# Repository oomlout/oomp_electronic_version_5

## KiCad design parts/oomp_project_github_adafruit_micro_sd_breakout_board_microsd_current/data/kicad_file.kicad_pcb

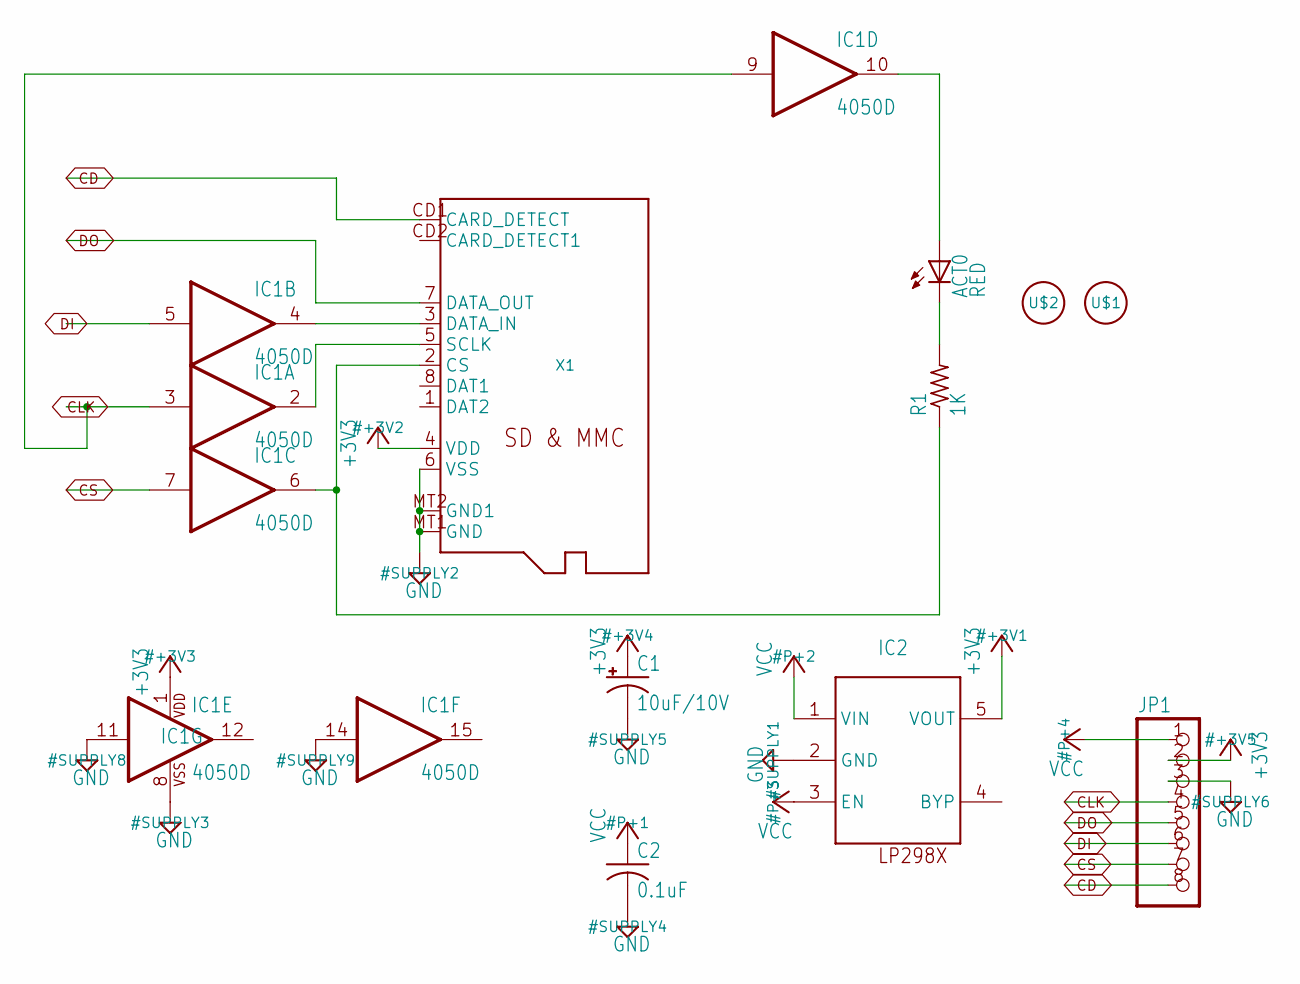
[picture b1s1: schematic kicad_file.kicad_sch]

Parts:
ACT0: RED; CHIP-LED0805
C1: 10uF/10V; A_3216-18R
C2: 0.1uF; C0805K
IC1: 4050D; SO16
IC2: LP298XS; SOT23-5L
JP1: PINHD-1X8BIG; 1X08-BIG
R1: 1K; R0805
U$1, U$2: FIDUCIAL; FIDUCIAL_1MM
X1: MICROSD

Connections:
+3V3: C1.+, IC1.1 (VDD), IC2.5 (VOUT), JP1.2, X1.4 (VDD)
CD: JP1.8, X1.CD1 (CARD_DETECT)
CLK: IC1.3 (I), IC1.9 (I), JP1.4
CS: IC1.7 (I), JP1.7
DI: IC1.5 (I), JP1.6
DO: JP1.5, X1.7 (DATA_OUT)
GND: C1.-, C2.2, IC1.8 (VSS), IC1.11 (I), IC1.14 (I), IC2.2 (GND), JP1.3, X1.6 (VSS), X1.MT1 (GND), X1.MT2 (GND1)
unnamed: ACT0.A, IC1.10 (O)
unnamed: IC1.2 (O), X1.5 (SCLK)
unnamed: IC1.6 (O), R1.1, X1.2 (CS)
unnamed: ACT0.C, R1.2
unnamed: IC1.4 (O), X1.3 (DATA_IN)
VCC: C2.1, IC2.1 (VIN), IC2.3 (EN), JP1.1

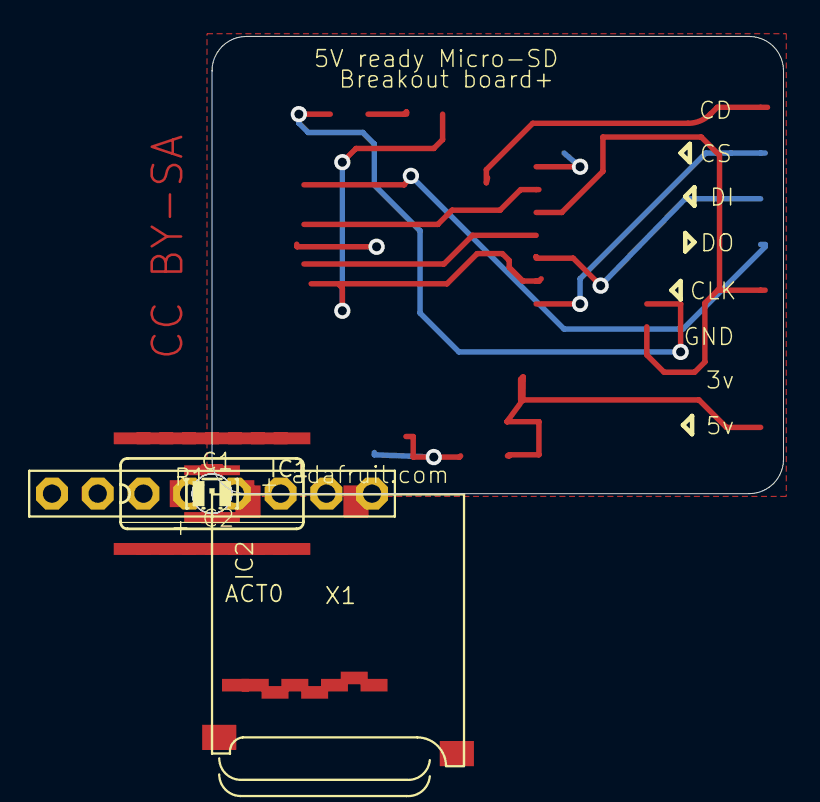
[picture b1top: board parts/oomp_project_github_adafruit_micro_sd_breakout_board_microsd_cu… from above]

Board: 16 copper layers, 31.8 x 25.4 mm, 14 parts (0 on the bottom side), 13 nets.

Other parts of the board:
UNK_HOLE_0: dummyfp0
UNK_HOLE_1: dummyfp1
UNK_HOLE_2: dummyfp2
UNK_HOLE_3: dummyfp3

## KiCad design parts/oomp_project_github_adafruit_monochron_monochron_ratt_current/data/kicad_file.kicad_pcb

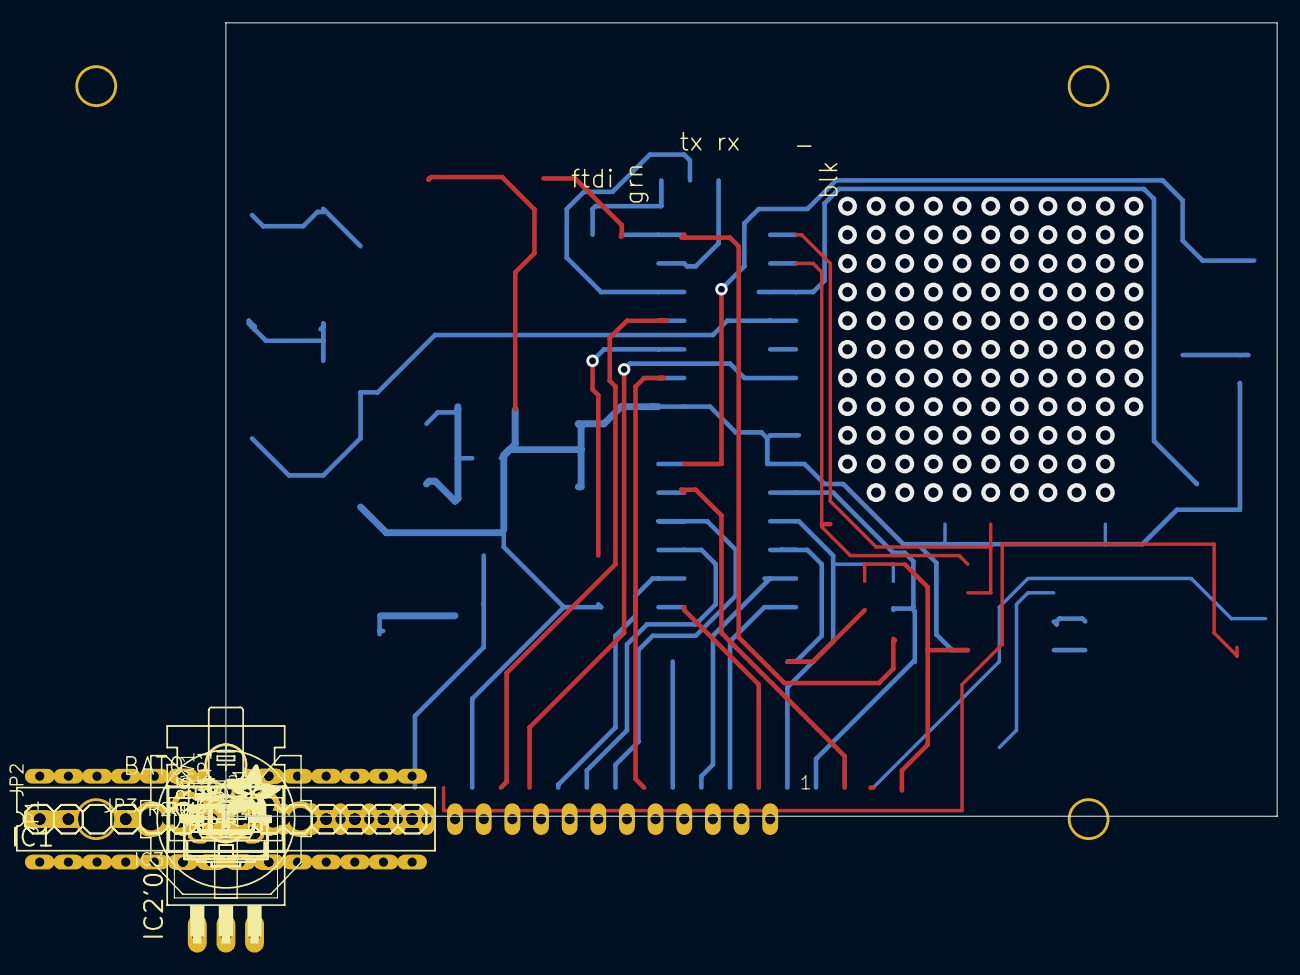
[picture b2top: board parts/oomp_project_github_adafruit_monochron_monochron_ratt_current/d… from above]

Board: 16 copper layers, 93.2 x 70.4 mm, 33 parts (1 on the bottom side), 17 nets.

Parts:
BAT0: CR1220; CR1220-THM
C1, C5: 0.1uF; C025-025X050
D1: 1N4004; DO41-10
IC1: ATMEGA168-20P; DIL28-3
IC2: 78L05Z; TO92
IC2'0: 7805T; TO220H
IC3: DS1307; DIL08
ISP0: ISP; 2X03
JP1: BRK1; 1X14
JP2: BRK2; 1X14
JP3: FTDI; 1X06
LED1: Red; LED3MM
Q1: 32.768; TC38H
R1: 1k; 0207_10
R2, R2'0: 100; 0207_10
R3, R4, R5, R6, R7: 1K; 0207_10
R8, R9: 2.2k; 0207_10
R10: 10K; 0207_10
S1, S2, S3: B3F-31XX
SP1: SPEAKER/PS12; PS12
SW1: OS102011MA1Q
TM1: 10K; CA6H
U$1: TS12864A; TS12864
U$2: http___www.ladyada.net_make_monochron

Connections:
+9V: C1.2, S1.1, S2.2, TM1.A
A: JP1.2, SW1.MT2
ALARM_SW: R6.1, R9.2
DB1: JP1.13, R3.1
DB2: JP1.12, R3.2
DB3: JP1.11, JP2.2
MOSI: IC1.4, JP2.1
unnamed: LED1.K, Q1.1, R7.1
unnamed: JP3.1, R2.2
unnamed: JP3.2, R2.1
unnamed: D1.C, S2.1
unnamed: R8.2, R9.1
unnamed: BAT0.+1, LED1.A, U$1.20
RST: IC1.5, R1.1, R5.1
RXD: R1.2, R5.2
SWITCHES: IC2'0.1, IC3.1, R7.2
VCC: IC1.2, IC2.1, IC3.2, ISP0.1, JP1.4, JP3.4, R2'0.2, R8.1, SP1.P$2, SW1.2, TM1.E

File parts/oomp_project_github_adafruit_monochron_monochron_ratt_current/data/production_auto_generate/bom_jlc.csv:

Comment,Designator,Footprint,LCSC Part #
,"S1,S2,S3",ratt-import-fps:B3F-31XX,
,U$2,ratt-import-fps:http___www.ladyada.net_make_monochron,
0.1uF,"C1,C5",ratt-import-fps:C025-025X050,
100,"R2,R2'0",ratt-import-fps:0207_10,
10K,R10,ratt-import-fps:0207_10,
10K,TM1,ratt-import-fps:CA6H,
1k,R1,ratt-import-fps:0207_10,
1K,"R3,R4,R5,R6,R7",ratt-import-fps:0207_10,
1N4004,D1,ratt-import-fps:DO41-10,
2.2k,"R8,R9",ratt-import-fps:0207_10,
32.768,Q1,ratt-import-fps:TC38H,
7805T,IC2'0,ratt-import-fps:TO220H,
78L05Z,IC2,ratt-import-fps:TO92,
ATMEGA168-20P,IC1,ratt-import-fps:DIL28-3,
BRK1,JP1,ratt-import-fps:1X14,
BRK2,JP2,ratt-import-fps:1X14,
CR1220,BAT0,ratt-import-fps:CR1220-THM,
DS1307,IC3,ratt-import-fps:DIL08,
FTDI,JP3,ratt-import-fps:1X06,
ISP,ISP0,ratt-import-fps:2X03,
OS102011MA1Q,SW1,ratt-import-fps:OS102011MA1Q,
Red,LED1,ratt-import-fps:LED3MM,
TS12864A,U$1,ratt-import-fps:TS12864,

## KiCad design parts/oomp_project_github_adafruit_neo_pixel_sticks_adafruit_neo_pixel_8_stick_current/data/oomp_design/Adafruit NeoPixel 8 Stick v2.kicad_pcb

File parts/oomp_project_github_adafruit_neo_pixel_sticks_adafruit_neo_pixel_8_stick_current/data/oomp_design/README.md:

# OOMP KiCad design copy

Open `Adafruit NeoPixel 8 Stick v2.kicad_pro` (or the `.kicad_pcb` / `.kicad_sch`) in KiCad. Local OOMP libraries are under `libraries/`. Original inputs are preserved in [../original/](../original/).

Only verified unchanged installed KiCad defaults were renamed. Modified, custom, unmatched and unavailable items remain unchanged. Soldering variants are never swapped during conversion. Existing pad coordinates, nets and UUIDs are preserved.

See [conversion_report.yaml](conversion_report.yaml) for every conversion and skip. Copy this directory before editing; regeneration refuses to overwrite edited design files.

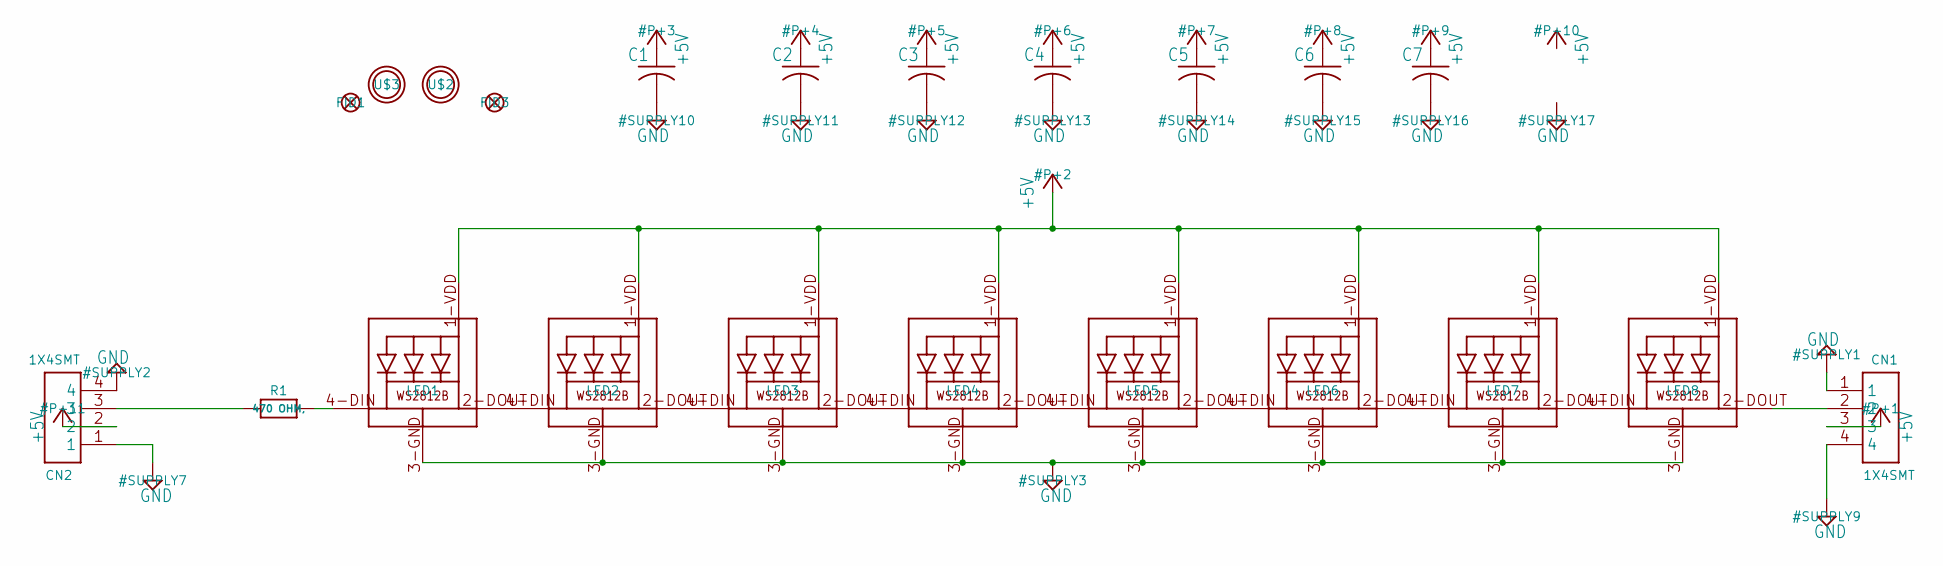
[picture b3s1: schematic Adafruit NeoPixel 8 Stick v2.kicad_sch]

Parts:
C1, C2, C3, C4, C5, C6, C7: C-USC0805K; C0805K
CN1, CN2: 1X4SMT; 1X4-SMT
FID1, FID3: FIDUCIAL""; FIDUCIAL_1MM
LED1, LED2, LED3, LED4, LED5, LED6, LED7, LED8: WS2812B5050; WS2812B
R1: 470 OHM,; _0805MP
U$2, U$3: MOUNTINGHOLE2.0; MOUNTINGHOLE_2.0_PLATED

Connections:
+5V: C1.1, C2.1, C3.1, C4.1, C5.1, C6.1, C7.1, CN1.3, CN2.2, LED1.1-VDD (VDD), LED2.1-VDD (VDD), LED3.1-VDD (VDD), LED4.1-VDD (VDD), LED5.1-VDD (VDD), LED6.1-VDD (VDD), LED7.1-VDD (VDD), LED8.1-VDD (VDD)
GND: C1.2, C2.2, C3.2, C4.2, C5.2, C6.2, C7.2, CN1.1, CN1.4, CN2.1, CN2.4, LED1.3-GND (GND), LED2.3-GND (GND), LED3.3-GND (GND), LED4.3-GND (GND), LED5.3-GND (GND), LED6.3-GND (GND), LED7.3-GND (GND), LED8.3-GND (GND)
unnamed: LED1.2-DOUT (DO), LED2.4-DIN (DI)
unnamed: LED2.2-DOUT (DO), LED3.4-DIN (DI)
unnamed: LED3.2-DOUT (DO), LED4.4-DIN (DI)
unnamed: LED4.2-DOUT (DO), LED5.4-DIN (DI)
unnamed: LED5.2-DOUT (DO), LED6.4-DIN (DI)
unnamed: LED6.2-DOUT (DO), LED7.4-DIN (DI)
unnamed: LED7.2-DOUT (DO), LED8.4-DIN (DI)
unnamed: CN2.3, R1.1
unnamed: CN1.2, LED8.2-DOUT (DO)
unnamed: LED1.4-DIN (DI), R1.2

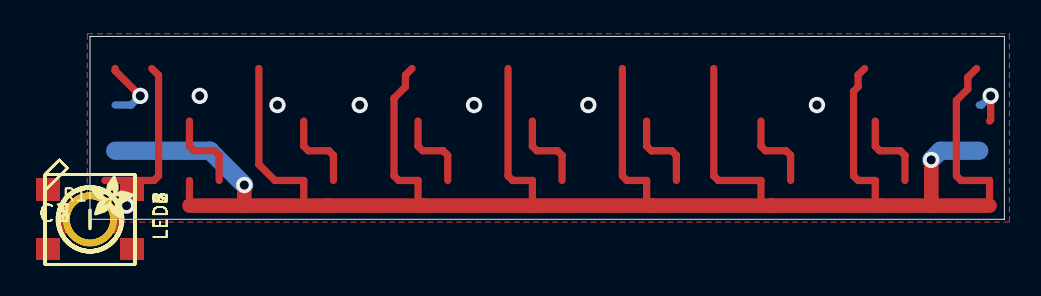
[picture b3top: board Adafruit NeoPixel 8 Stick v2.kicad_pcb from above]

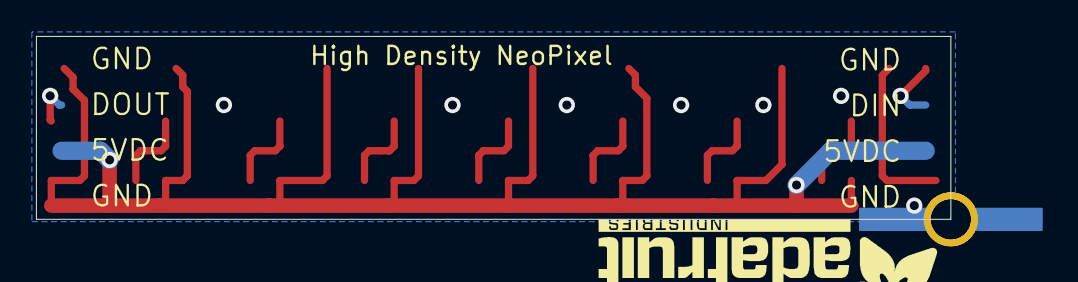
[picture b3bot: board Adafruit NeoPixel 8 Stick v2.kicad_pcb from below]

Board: 2 copper layers, 50.8 x 10.2 mm, 24 parts (3 on the bottom side), 12 nets.

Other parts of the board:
U$1: ADAFRUIT_TEXT_20MM
U$4: ADAFRUIT_2.5MM

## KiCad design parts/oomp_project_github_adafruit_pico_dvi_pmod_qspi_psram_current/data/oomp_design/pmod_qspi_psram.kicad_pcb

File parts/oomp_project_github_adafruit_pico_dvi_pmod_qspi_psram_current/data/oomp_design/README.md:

# OOMP KiCad design copy

Open `pmod_qspi_psram.kicad_pro` (or the `.kicad_pcb` / `.kicad_sch`) in KiCad. Local OOMP libraries are under `libraries/`. Original inputs are preserved in [../original/](../original/).

Only verified unchanged installed KiCad defaults were renamed. Modified, custom, unmatched and unavailable items remain unchanged. Soldering variants are never swapped during conversion. Existing pad coordinates, nets and UUIDs are preserved.

See [conversion_report.yaml](conversion_report.yaml) for every conversion and skip. Copy this directory before editing; regeneration refuses to overwrite edited design files.

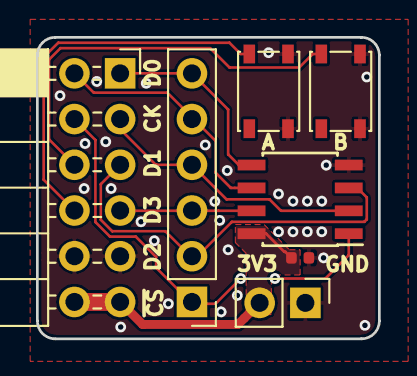
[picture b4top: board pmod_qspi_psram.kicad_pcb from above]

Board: 2 copper layers, 19.0 x 16.8 mm, 7 parts (0 on the bottom side), 10 nets.

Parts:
C1: 100n; C_0402_1005Metric
J1: 2.54mm_2x06; PinSocket_2x06_P2.54mm_Horizontal
J2: Conn_01x06; PinHeader_1x06_P2.54mm_Vertical
J3: Conn_01x02; PinHeader_1x02_P2.54mm_Vertical
SW1, SW2: SW_Push; SW_SPST_PTS815
U1: LY68L6400; SOIC-8_3.9x4.9mm_P1.27mm

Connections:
+3V3: C1.1, J1.11, J1.12, J3.2, U1.8
/BUTTON_A: J1.8, SW1.1
/BUTTON_B: J1.6, SW2.1
/SCK: J1.2, J2.5, U1.6
/SD0: J1.1, J2.6, U1.5
/SD1: J1.3, J2.4, U1.2
/SD2: J1.5, J2.2, U1.3
/SD3: J1.7, J2.3, U1.7
/~CS~: J1.4, J2.1, U1.1
GND: C1.2, J1.9, J1.10, J3.1, SW1.2, SW2.2, U1.4

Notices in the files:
parts/oomp_project_github_adafruit_micro_sd_breakout_board_microsd_current/data/kicad_file.kicad_pcb:
CC BY-SA
